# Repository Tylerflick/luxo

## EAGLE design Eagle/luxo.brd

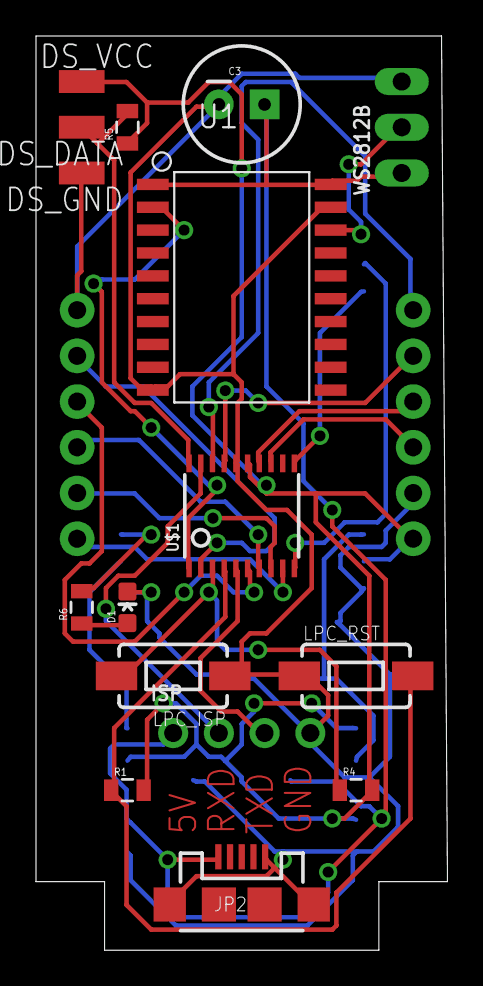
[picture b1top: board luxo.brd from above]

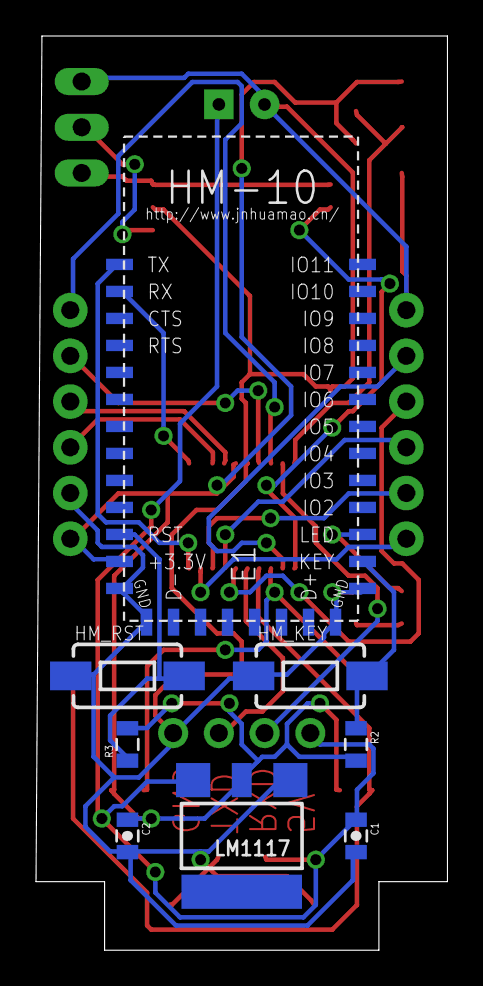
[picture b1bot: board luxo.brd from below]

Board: 2 copper layers, 22.9 x 50.8 mm, 26 parts (8 on the bottom side), 25 nets.

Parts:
C1, C2: 10uf; 0805-CAP
C3: 100uf; CPOL-RADIAL-100UF-25V
D1: BLUE; LED-0603
DS_DATA: SMD1,27-2,54
DS_GND: SMD1,27-2,54
DS_VCC: SMD1,27-2,54
E1: HM-10-BOARD; 26.9X13X2.2_BOARD
HM_KEY: SWITCH-MOMENTARY-2SMD-1101NE; TACTILE-SWITCH-1101NE
HM_RST: SWITCH-MOMENTARY-2SMD-1101NE; TACTILE-SWITCH-1101NE
ISP: ISP Header; 1X04_ROUND
JP2: USB-MICROB
LEFT_BANK: 1X06_ROUND_76
LM1117: 3.3V; SOT223-W
LPC_ISP: SWITCH-MOMENTARY-2SMD-1101NE; TACTILE-SWITCH-1101NE
LPC_RST: SWITCH-MOMENTARY-2SMD-1101NE; TACTILE-SWITCH-1101NE
R1: 10k; 0805
R2, R3: 1k; 0805
R4: 50k; 0805
R5: 4.7k; 0805
R6: 470; 0805
RIGHT_BANK: 1X06_ROUND_76
U1: 74HCT245; SOP20-10.65
U$1: LPC812M101JDH20; TSSOP20
WS2812B: WS2812B; 1X03_OVAL

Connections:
3.3V: C2.1, DS_VCC.1, E1.12, LM1117.2, R1.2, R2.2, R3.2, R4.2, R5.1, RIGHT_BANK.1, U$1.15
5V: C1.1, C3.1, ISP.1, JP2.VBUS, LM1117.3, U1.1, U1.20, WS2812B.1
DS_DATA: DS_DATA.1, R5.2, U$1.20
GND: C1.2, C2.2, C3.2, D1.C, DS_GND.1, E1.13, E1.14, E1.21, E1.22, HM_KEY.1, HM_RST.1, ISP.4, JP2.GND, JP2.MT1, JP2.MT2, LEFT_BANK.6, LM1117.1, LPC_ISP.1, LPC_RST.1, RIGHT_BANK.2, U1.10, U1.19, U$1.16, WS2812B.3
HM_LED: E1.24, R6.2
HM_RST: E1.11, HM_RST.2, R3.1
HM_RX: E1.2, U$1.11
HM_TX: E1.1, U$1.10
ISP_PN: LPC_ISP.2, R4.1, U$1.3
KEY: E1.23, HM_KEY.2, R2.1
unnamed: D1.A, R6.1
P2: LEFT_BANK.5, U$1.2
P5: ISP.3, U$1.5
P6: LEFT_BANK.4, U$1.6
P7: LEFT_BANK.3, U$1.7
P8: LEFT_BANK.2, U$1.8
P9: LEFT_BANK.1, U$1.9
P13: RIGHT_BANK.3, U$1.13
P14: RIGHT_BANK.4, U$1.14
P17: RIGHT_BANK.5, U$1.17
P18: RIGHT_BANK.6, U$1.18
P19: ISP.2, U$1.19
RESET: LPC_RST.2, R1.1, U$1.4
WS_RX: U1.18, WS2812B.2
WS_TX: U1.2, U$1.1

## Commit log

2015-06-09 Add Eagle schematic
    Added the initial Eagle schematic file for the LPC812 controller.
2015-06-09 Add LM1117 LVR from Sparkfun Eagle Library
2015-06-11 Add voltage regulator to schematic
    Added 3.3v voltage regulator and 2 switches needed for LPC812 flashing.
2015-06-14 Add logic level shifter
2015-06-15 Add 74HCT245 level shifter
2015-06-16 Finish V 1.0

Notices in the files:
parts and their libraries:
SparkFun-Capacitors: Licensing: Creative Commons ShareAlike 4.0 International - https://creativecommons.org/licenses/by-sa/4.0
microbuilder: This work is placed in the public domain, and may be freely used for commercial and non-commercial work with the following conditions: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
